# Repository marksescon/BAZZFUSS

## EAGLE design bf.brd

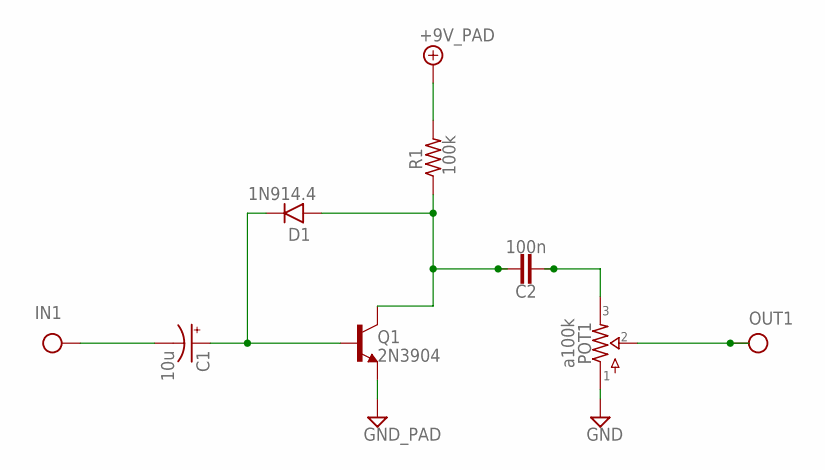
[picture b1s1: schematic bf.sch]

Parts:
C1: 10u; 050_020
C2: 100n; 0.2".SML
D1: 1N914.4; DO35-4
GND2: GND_PAD; SQUARE
IN1: IN; SQUARE
OUT1: OUT; SQUARE
POT1: a100k; 16MM_B.MOUNT
Q1: 2N3904; TO92-
R1: 100k; R0207/4
V1: +9V_PAD; SQUARE

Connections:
+9V: R1.2, V1.1
GND: GND2.1, POT1.1, Q1.3 (E)
IN: C1.-, IN1.1
unnamed: C1.+, D1.C, Q1.2 (B)
unnamed: C2.1, D1.A, Q1.1 (C), R1.1
unnamed: C2.2, POT1.3
OUT: OUT1.1, POT1.2

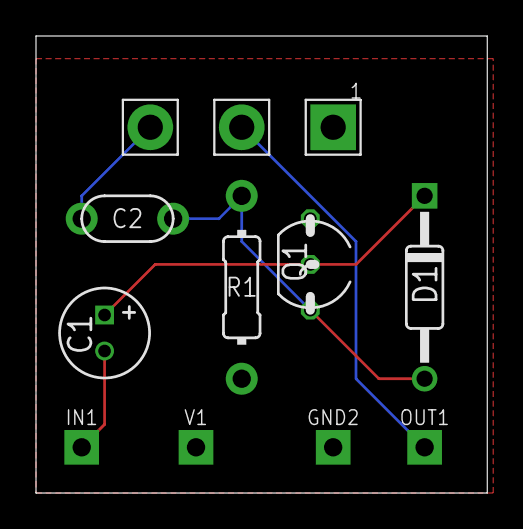
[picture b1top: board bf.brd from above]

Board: 2 copper layers, 25.1 x 25.4 mm, 10 parts (0 on the bottom side), 7 nets.
